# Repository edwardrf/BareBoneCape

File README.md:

# IO Cape
### A simple BeagleBone Black Cape extending the pwm and GPIO pins with an i2c ADC chip for 5V ADC input (ADS7828) in KiCad

This board also has a connection designed for a proprietary 9 axis board using Bosch BMX055 using i2c interface

I am sorry for the poor quality and poor documentation for this project, this is largly due to my lazyness technical inability.

Note: even though the lib i created is named txb0108b, the actual chip we used is TXS0108E, which supports both open-drain (for i2c) and push-pull (for uart) devices.

####*WARNING: DO NOT BUILD THE BOARD*
For the master branch, we have manufactured one, and realized BBB will not boot with this cape on, we had to boot bbb and then put the cape to boot the device correctly. After some testing, it seems the way I powered up the devices are over simplified, which results in unexpected behavior in the buffer chips during boot up and some of the chips are connected to the pins which are shared with the SYS_BOOT and  EMMC pins, specificly, the P8_31 to P8_46. This board boots with SD card with no problem though.
We will fix these issues soon. We will keep develop the master branch as a general IO expansion board for BBB and in the mean time ...

### Plane version ###
We are creating a newer version which is designed for our flight controller (in the plane branch), this new version would be less general, but some of the main features are:
* Embedded ATmega328p for some low level processing and take over the control when BBB is not available
* builtin BMX055 (9 axis)  and BMP180 (barometer)  chips on i2c bus 2 (i2c2)
* PCA9685 as the PWM output driver which would give us more precision, more PWM output channels and maintain output when BBB is not available.

## Pin Mapping

* Buffer #0  on the right top

|   Name    |   BeagleBone Pin ID   | GPIO  	|
|-----------|-----------------------|-----------|
|	D70		|	P8_45				|GPIO2_6	|
|	D71		|	P8_46				|GPIO2_7	|
|	D72		|	P8_43				|GPIO2_8	|
|	D73		|	P8_44				|GPIO2_9	|
|	D74		|	P8_41				|GPIO2_10	|
|	D75		|	P8_42				|GPIO2_11	|
|	D76		|	P8_39				|GPIO2_12	|
|	D77		|	P8_40				|GPIO2_13	|

* Buffer #1 on the left

|   Name    |   BeagleBone Pin ID   | GPIO  	|
|-----------|-----------------------|-----------|
|	P9_31	|	P9_31				|		|
|	P9_29	|	P9_29				|		|
|	P9_14	|	P9_14				|		|
|	P9_16	|	P9_16				|		|
|	P9_19	|	P9_19				|		|
|	P8_13	|	P8_13				|		|
|	P9_42	|	P9_42				|		|
|	P9_28	|	P9_28				|		|

* Buffer #2 on the middle

|   Name    |   BeagleBone Pin ID   | GPIO  	|
|-----------|-----------------------|-----------|
|	D32		|	P8_25				|GPIO1_0	|
|	D33		|	P8_24				|GPIO1_1	|
|	D34		|	P8_5				|GPIO1_2	|
|	D35		|	P8_6				|GPIO1_3	|
|	D36		|	P8_23				|GPIO1_4	|
|	D37		|	P8_22				|GPIO1_5	|
|	D38		|	P8_3				|GPIO1_6	|
|	D39		|	P8_4				|GPIO1_7	|

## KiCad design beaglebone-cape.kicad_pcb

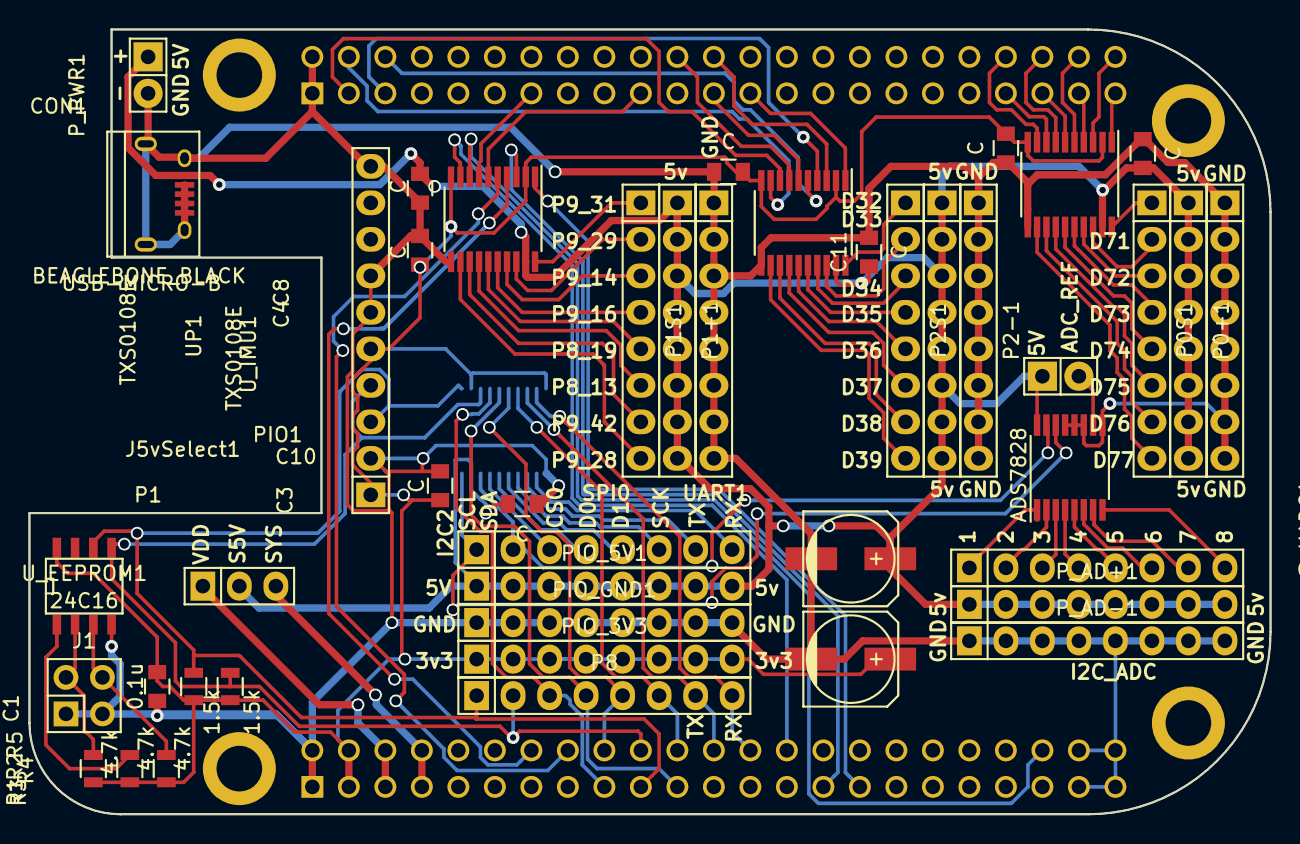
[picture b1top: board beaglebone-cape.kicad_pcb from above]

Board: 2 copper layers, 86.4 x 54.6 mm, 46 parts (1 on the bottom side), 81 nets.

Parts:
C1: 0.1u; C_0805
C2, C7: CP2; c_elec_6.3x5.7
C3, C4, C5, C6, C8, C9, C10, C11: C; C_0805
CON1: USB-MICRO-B; USB_Micro-B
J1: CONN_02X02; Pin_Header_Straight_2x02
J5vSelect1: CONN_01X03; Pin_Header_Straight_1x03
J_ADC_REF1: CONN_01X02; Pin_Header_Straight_1x02
P0+1, P0-1, P0S1, P1+1, P1-1, P1S1, P2+1, P2-1, P2S1, P8: CONN_01X08; Pin_Header_Straight_1x08
P1: BEAGLEBONE_BLACK
PIO1: CONN_01X08; Pin_Header_Straight_1x08
PIO_3V3, PIO_5V1: CONN_01X08; Pin_Header_Straight_1x08
PIO_GND1: CONN_01X08; Pin_Header_Straight_1x08
P_AD1: CONN_01X08; Pin_Header_Straight_1x08
P_AD+1: CONN_01X08; Pin_Header_Straight_1x08
P_AD-1: CONN_01X08; Pin_Header_Straight_1x08
P_PWR1: CONN_01X02; Pin_Header_Straight_1x02
R1, R2, R3: 4.7k; R_0805
R4, R5: 1.5k; R_0805
UADC1: ADS7828; TSSOP-16_4.4x5mm_Pitch0.65mm
UP0, UP1, UP2: TXS0108E; TSSOP-20_4.4x6.5mm_Pitch0.65mm
UPIO1: TXS0108E; TSSOP-20_4.4x6.5mm_Pitch0.65mm
U_EEPROM1: 24C16; SOIC-8-W
U_IMU1: BMX055-Breakout; Pin_Header_Straight_1x10

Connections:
/A0: R3.2, U_EEPROM1.1
/A1: J1.2, R1.2, U_EEPROM1.2
/A2: J1.4, R2.2, U_EEPROM1.3
/DC_3.3V: C1.1, C2.1, C3.1, C4.1, C5.1, C6.1, P1.B3, P1.B4, PIO_3V3.1, PIO_3V3.2, PIO_3V3.3, PIO_3V3.4, PIO_3V3.5, PIO_3V3.6, PIO_3V3.7, PIO_3V3.8, R1.1, R2.1, R3.1, R4.1, R5.1, UP0.2, UP0.10, UP1.2, UP1.10, UP2.2, UP2.10, UPIO1.2, UPIO1.10, U_EEPROM1.8, U_IMU1.1, U_IMU1.5
/ECAPPWM0: P1.B42, UP1.8
/ECAPPWM2: P1.B28, UP1.9
/EHRPWM0A: P1.B31, UP1.1
/EHRPWM0B: P1.B29, UP1.3
/EHRPWM1A: P1.B14, UP1.4
/EHRPWM1B: P1.B16, UP1.5
/EHRPWM2A: P1.A19, UP1.6
/EHRPWM2B: P1.A13, UP1.7
/GPIO1_0: P1.A25, UP2.1
/GPIO1_1: P1.A24, UP2.3
/GPIO1_2: P1.A5, UP2.4
/GPIO1_3: P1.A6, UP2.5
/GPIO1_4: P1.A23, UP2.6
/GPIO1_5: P1.A22, UP2.7
/GPIO1_6: P1.A3, UP2.8
/GPIO1_7: P1.A4, UP2.9
/GPIO2_6: P1.A45, UP0.1
/GPIO2_7: P1.A46, UP0.3
/GPIO2_8: P1.A43, UP0.4
/GPIO2_9: P1.A44, UP0.5
/GPIO2_10: P1.A41, UP0.6
/GPIO2_11: P1.A42, UP0.7
/GPIO2_12: P1.A39, UP0.8
/GPIO2_13: P1.A40, UP0.9
/I2C1_SCL: P1.B17, P8.3, UPIO1.4
/I2C1_SDA: P1.B18, P8.5, UPIO1.6
/I2C2_SCL: P1.B19, P8.1, R4.2, UPIO1.1, U_EEPROM1.6, U_IMU1.3
/I2C2_SDA: P1.B20, P8.2, R5.2, UPIO1.3, U_EEPROM1.5, U_IMU1.4
/P_GPIO_32: P2S1.1, UP2.20
/P_GPIO_33: P2S1.2, UP2.18
/P_GPIO_34: P2S1.3, UP2.17
/P_GPIO_35: P2S1.4, UP2.16
/P_GPIO_36: P2S1.5, UP2.15
/P_GPIO_37: P2S1.6, UP2.14
/P_GPIO_38: P2S1.7, UP2.13
/P_GPIO_39: P2S1.8, UP2.12
/P_GPIO_70: P0S1.1, UP0.20
/P_GPIO_71: P0S1.2, UP0.18
/P_GPIO_72: P0S1.3, UP0.17
/P_GPIO_73: P0S1.4, UP0.16
/P_GPIO_74: P0S1.5, UP0.15
/P_GPIO_75: P0S1.6, UP0.14
/P_GPIO_76: P0S1.7, UP0.13
/P_GPIO_77: P0S1.8, UP0.12
/P_I2C2_SCL: PIO1.1, UADC1.14, UPIO1.20
/P_I2C2_SDA: PIO1.2, UADC1.15, UPIO1.18
/P_PWM_P8_13: P1S1.6, UP1.14
/P_PWM_P8_19: P1S1.5, UP1.15
/P_PWM_P9_14: P1S1.3, UP1.17
/P_PWM_P9_16: P1S1.4, UP1.16
/P_PWM_P9_28: P1S1.8, UP1.12
/P_PWM_P9_29: P1S1.2, UP1.18
/P_PWM_P9_31: P1S1.1, UP1.20
/P_PWM_P9_42: P1S1.7, UP1.13
/P_SPI0_CS0: PIO1.3, UPIO1.17
/P_SPI0_D0: PIO1.4, UPIO1.16
/P_SPI0_D1: PIO1.5, UPIO1.15
/P_SPI0_SCLK: PIO1.6, UPIO1.14
/P_UART1_RXD: PIO1.8, UPIO1.12
/P_UART1_TXD: PIO1.7, UPIO1.13
/SHLD_5V: C7.1, C8.1, C9.1, C10.1, C11.1, CON1.1, J5vSelect1.2, J_ADC_REF1.1, P0+1.1, P0+1.2, P0+1.3, P0+1.4, P0+1.5, P0+1.6, P0+1.7, P0+1.8, P1+1.1, P1+1.2, P1+1.3, P1+1.4, P1+1.5, P1+1.6, P1+1.7, P1+1.8, P2+1.1, P2+1.2, P2+1.3, P2+1.4, P2+1.5, P2+1.6, P2+1.7, P2+1.8, PIO_5V1.1, PIO_5V1.2, PIO_5V1.3, PIO_5V1.4, PIO_5V1.5, PIO_5V1.6, PIO_5V1.7, PIO_5V1.8, P_AD+1.1, P_AD+1.2, P_AD+1.3, P_AD+1.4, P_AD+1.5, P_AD+1.6, P_AD+1.7, P_AD+1.8, P_PWR1.1, UADC1.16, UP0.19, UP1.19, UP2.19, UPIO1.19
/SPI0_D0: P1.B21, P8.4, UPIO1.5
/SPI0_SCLK: P1.B22, P8.6, UPIO1.7
/SYS_5V: J5vSelect1.3, P1.B7, P1.B8
/UART1_RXD: P1.B26, P8.8, UPIO1.9
/UART1_TXD: P1.B24, P8.7, UPIO1.8
/VDD_5V: J5vSelect1.1, P1.B5, P1.B6
GND: C1.2, C2.2, C3.2, C4.2, C5.2, C6.2, C7.2, C8.2, C9.2, C10.2, C11.2, CON1.2, CON1.3, CON1.4, CON1.5, CON1.6, CON1.7, CON1.8, CON1.9, J1.1, J1.3, P0-1.1, P0-1.2, P0-1.3, P0-1.4, P0-1.5, P0-1.6, P0-1.7, P0-1.8, P1.A1, P1.A2, P1.B1, P1.B2, P1.B43, P1.B44, P1.B45, P1.B46, P1-1.1, P1-1.2, P1-1.3, P1-1.4, P1-1.5, P1-1.6, P1-1.7, P1-1.8, P2-1.1, P2-1.2, P2-1.3, P2-1.4, P2-1.5, P2-1.6, P2-1.7, P2-1.8, PIO_GND1.1, PIO_GND1.2, PIO_GND1.3, PIO_GND1.4, PIO_GND1.5, PIO_GND1.6, PIO_GND1.7, PIO_GND1.8, P_AD-1.1, P_AD-1.2, P_AD-1.3, P_AD-1.4, P_AD-1.5, P_AD-1.6, P_AD-1.7, P_AD-1.8, P_PWR1.2, UADC1.9, UADC1.11, UADC1.12, UADC1.13, UP0.11, UP1.11, UP2.11, UPIO1.11, U_EEPROM1.4, U_IMU1.2, U_IMU1.6, U_IMU1.7, U_IMU1.10
unnamed: J_ADC_REF1.2, UADC1.10
unnamed: P_AD1.1, UADC1.1
unnamed: P_AD1.2, UADC1.2
unnamed: P_AD1.3, UADC1.3
unnamed: P_AD1.4, UADC1.4
unnamed: P_AD1.5, UADC1.5
unnamed: P_AD1.6, UADC1.6
unnamed: P_AD1.7, UADC1.7
unnamed: P_AD1.8, UADC1.8

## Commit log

2015-01-22 Create the io cape base on the barebone cape
2015-02-16 add pin mapping
2015-02-16 add up1 mapping
2015-02-16 add buffer 2 mapping
2015-02-16 fix format
2015-02-28 Some small update, before forking for plane project
2015-03-04 Added new symbols for new ICs, created gitignore
2015-03-04 added back txs0108e
2015-03-04 Added back txs0108e lib
2015-03-04 Explain the difference between the 2 branches
2015-03-04 Add the cache lib
2015-03-04 Create schematics for plane shield
